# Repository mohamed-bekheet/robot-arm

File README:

This respositry specially for DR.Elhabrook project (3rd year power Dep.)
This project aim to make robot arm on self-balancing robot with magnet levitation hand can move in a map and determinte its coordinates 
A plus cinnect with mobile application or pc serial software.

Team Members:
1.Mohamed Moustafa ALy Abd el-latif 18011618 @m-maker2023 @m-maker2023
2.Mohamed Sedeek Mohamed Sedeek 18011496 @
//TODO@m-maker2023

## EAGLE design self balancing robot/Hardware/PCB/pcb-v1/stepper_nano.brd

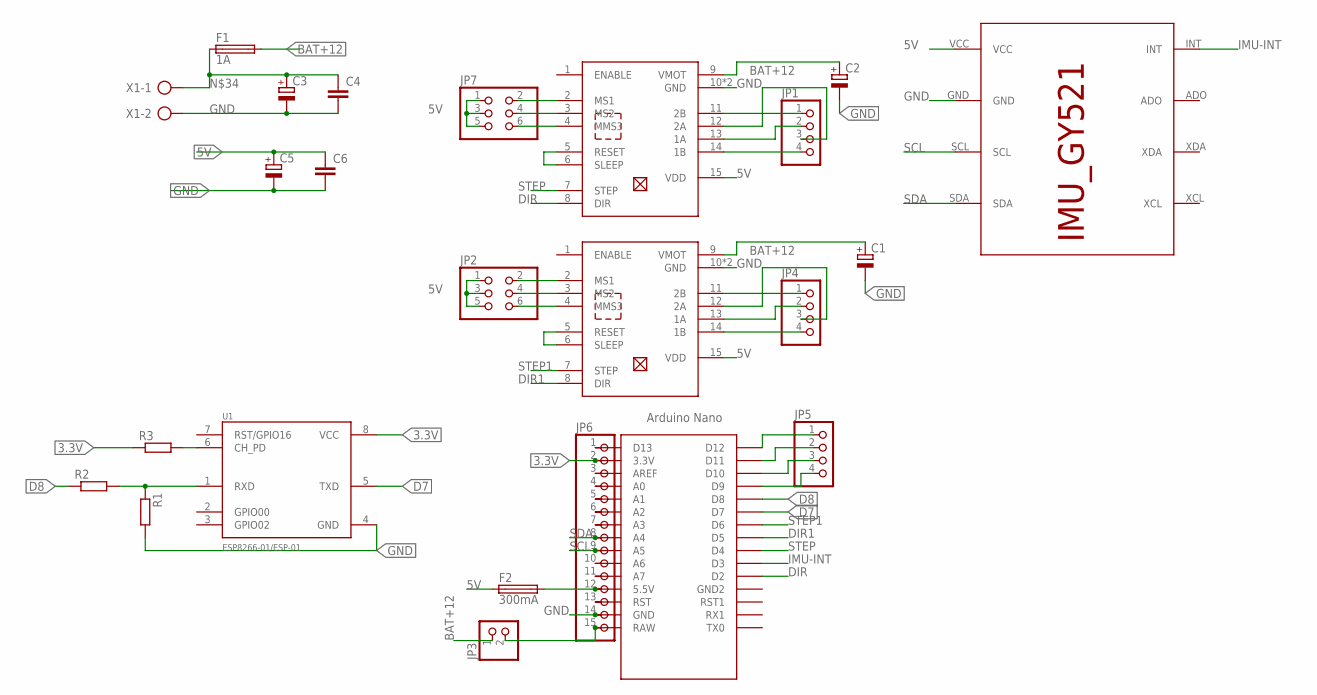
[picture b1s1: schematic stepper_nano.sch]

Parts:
C1, C2, C3, C5: CPOL-EUE2-5; E2-5
C4, C6: C-EU025-024X044; C025-024X044
F1: 1A; SH22
F2: 300mA; SH22
JP1, JP4, JP5: PINHD-1X4; 1X04
JP2, JP7: PINHD-2X3; 2X03
JP3: PINHD-1X2; 1X02
JP6: PINHD-1X15; 1X15
R1: R-EU_0204/5; 0204/5
R2, R3: R-EU_0204/7; 0204/7
U1: ESP8266-01/ESP-01; XCVR_ESP8266-01/ESP-01
U$1: ARDUINO_NANO; NANO
U$2: IMU-MPU; IMU_GY521
U$3, U$4: STEPPER-DRIVER; A4988-DRIVER
X1: AK300/2

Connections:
3.3V: JP6.2, R3.1, U1.8 (VCC), U$1.3.3V
5V: C5.+, C6.1, F2.1, JP2.1, JP2.3, JP2.5, JP7.1, JP7.3, JP7.5, U$2.VCC, U$3.15 (VDD), U$4.15 (VDD)
BAT+12: C1.+, C2.+, F1.2, JP3.1, U$3.9 (VMOT), U$4.9 (VMOT)
D7: U1.5 (TXD), U$1.D7
D8: R2.1, U$1.D8
DIR: U$1.D2, U$3.8 (DIR)
DIR1: U$1.D5, U$4.8 (DIR)
FUSE-5V: F2.2, JP6.12, U$1.5V (5.5V)
GND: C1.-, C2.-, C3.-, C4.2, C5.-, C6.2, JP6.14, R1.2, U1.4 (GND), U$1.GND, U$2.GND, U$3.10 (GND), U$3.16 (GND), U$4.10 (GND), U$4.16 (GND), X1.2
IMU-INT: U$1.D3, U$2.INT
unnamed: JP1.1, U$3.11 (2B)
unnamed: JP1.4, U$3.14 (1B)
unnamed: JP1.2, U$3.13 (1A)
unnamed: JP1.3, U$3.12 (2A)
unnamed: JP4.1, U$4.11 (2B)
unnamed: JP4.4, U$4.14 (1B)
unnamed: JP4.2, U$4.13 (1A)
unnamed: JP4.3, U$4.12 (2A)
unnamed: JP7.2, U$3.2 (MS1)
unnamed: JP7.4, U$3.3 (MS2)
unnamed: JP7.6, U$3.4 (MMS3)
unnamed: U$3.5 (RESET), U$3.6 (SLEEP)
unnamed: JP2.2, U$4.2 (MS1)
unnamed: JP2.4, U$4.3 (MS2)
unnamed: JP2.6, U$4.4 (MMS3)
unnamed: U$4.5 (RESET), U$4.6 (SLEEP)
unnamed: R3.2, U1.6 (CH_PD)
unnamed: JP3.2, JP6.15, U$1.RAW
unnamed: JP5.4, U$1.D9
unnamed: JP5.3, U$1.D10
unnamed: R1.1, R2.2, U1.1 (RXD)
unnamed: JP5.2, U$1.D11
unnamed: JP5.1, U$1.D12
unnamed: JP6.1, U$1.D13
unnamed: JP6.3, U$1.AREF
unnamed: JP6.4, U$1.A0
unnamed: JP6.5, U$1.A1
unnamed: JP6.6, U$1.A2
unnamed: JP6.7, U$1.A3
unnamed: JP6.10, U$1.A6
unnamed: JP6.11, U$1.A7
unnamed: JP6.13, U$1.RST
unnamed: C3.+, C4.1, F1.1, X1.1
SCL: JP6.9, U$1.A5, U$2.SCL
SDA: JP6.8, U$1.A4, U$2.SDA
STEP: U$1.D4, U$3.7 (STEP)
STEP1: U$1.D6, U$4.7 (STEP)

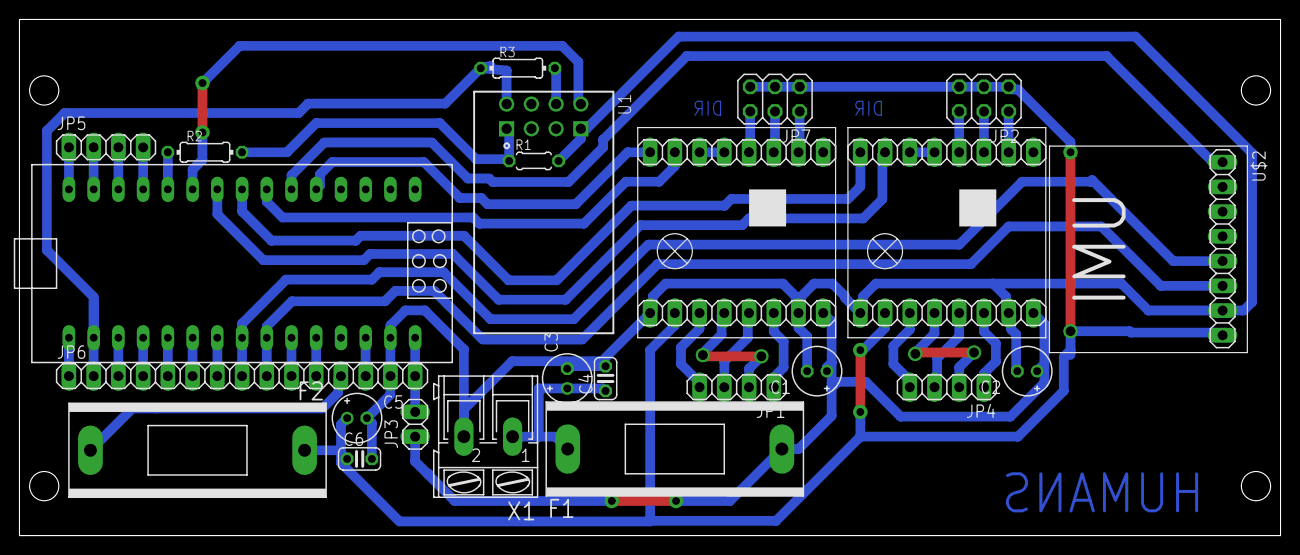
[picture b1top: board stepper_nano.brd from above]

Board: 2 copper layers, 129.5 x 53.0 mm, 24 parts (0 on the bottom side), 47 nets.

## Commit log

2021-10-19 add readme file for team members and project hint
2021-10-19 add new feature for right wheel
2021-10-19 add new member name(sedeek)
2021-11-04 add new projects
2021-11-08 UPDATE NEW FOLDERS
2021-11-08 chnge folder directory
2021-11-08 add name for code with timer for stepper motors
2021-11-14 last work with sedeek, momen and mohamed
2021-11-20 add a new project (Line Follower)
2021-11-20 update line follower
2021-11-21 farag edit
2021-11-21 update foldering
2021-11-21 test hi
2021-11-21 upload sedeek version
2021-11-21 nothing
2021-12-06 pid tested with timers for stepper puls generation
2021-12-06 test
2021-12-08 add code for dc motors
2021-12-27 khaled
2021-12-27 edit
2021-12-27 final code
2021-12-27 sedeek update app control
2021-12-28 last update for esp01 server
2021-12-28 arduino-selfbalance-last code
2022-01-02 latest update
2022-01-02 done
